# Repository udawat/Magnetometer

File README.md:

Magnetometer
============

Honeywell’s HMC5883L 3-Axis Magnetometer can measure both the direction and the magnitude of Earth’s magnetic fields. Think of it as a Digital Compass.

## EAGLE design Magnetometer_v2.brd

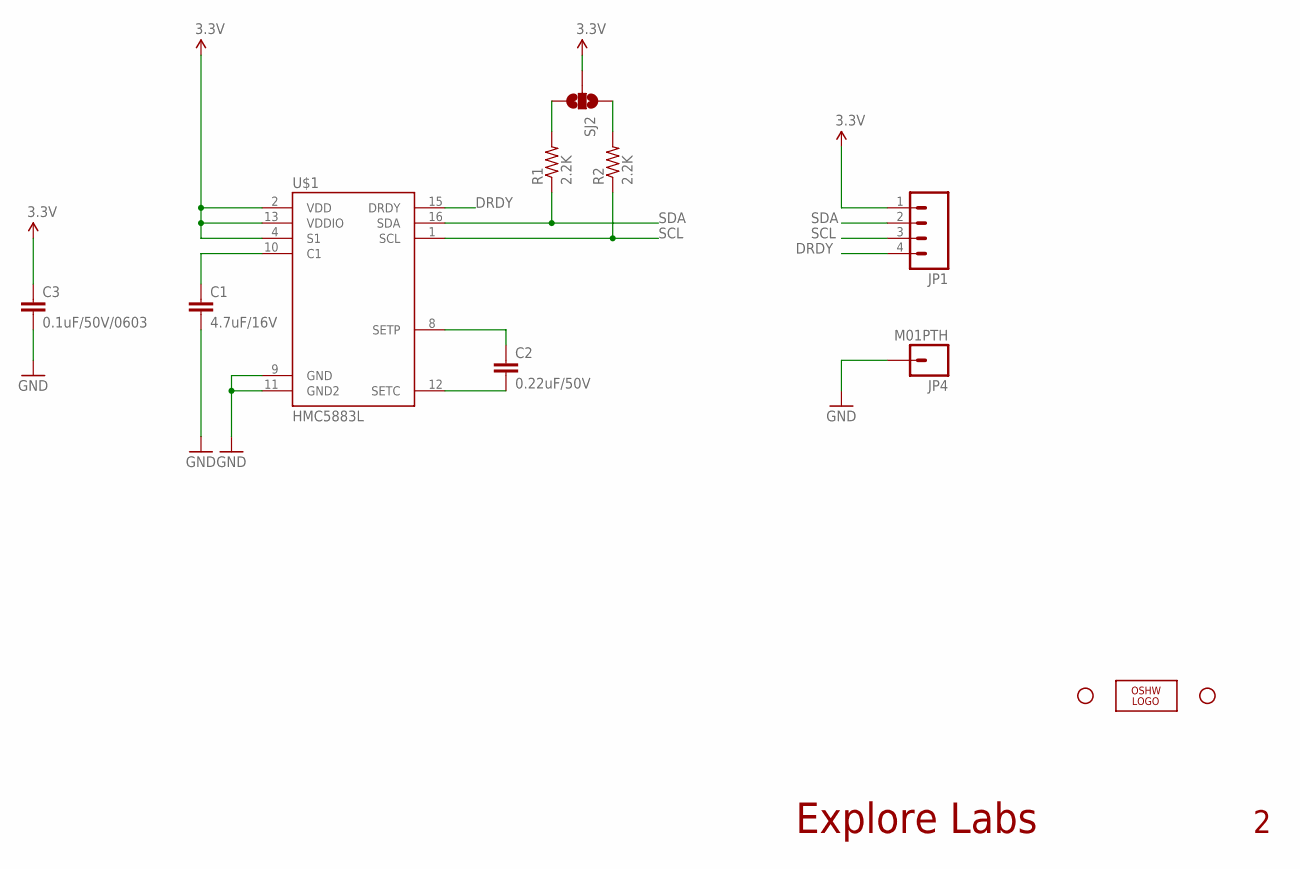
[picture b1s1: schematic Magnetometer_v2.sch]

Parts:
C1: 4.7uF/16V; 1206
C2: 0.22uF/50V; 1206
C3: 0.1uF/50V/0603; 0603-CAP
JP1: M04PTH; 1X04
JP2, JP3: STAND-OFFTIGHT; STAND-OFF-TIGHT
JP4: M01PTH; 1X01
LOGO1: OSHW_LOGO_FILLX0150-NT; OSHW_FILLX150_NOTEXT
R1, R2: 2.2K; 0603-RES
SJ2: SOLDERJUMPER_2WAYS; SJ_3
U$1: HMC5883L; LPCC16

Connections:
3.3V: C3.1, JP1.1, SJ2.2, U$1.2 (VDD), U$1.4 (S1), U$1.13 (VDDIO)
DRDY: JP1.4, U$1.15 (DRDY)
GND: C1.2, C3.2, JP4.1, U$1.9 (GND), U$1.11 (GND2)
unnamed: C2.1, U$1.8 (SETP)
unnamed: C1.1, U$1.10 (C1)
unnamed: R1.2, SJ2.3
unnamed: R2.2, SJ2.1
unnamed: C2.2, U$1.12 (SETC)
SCL: JP1.3, R2.1, U$1.1 (SCL)
SDA: JP1.2, R1.1, U$1.16 (SDA)

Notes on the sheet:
Explore Labs

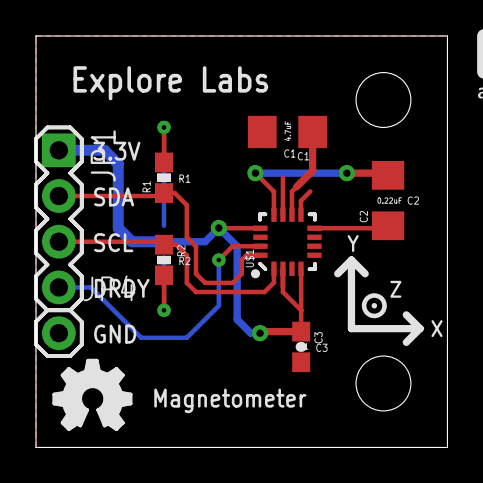
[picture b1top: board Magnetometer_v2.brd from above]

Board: 2 copper layers, 22.9 x 22.9 mm, 13 parts (1 on the bottom side), 10 nets.

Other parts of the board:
U$2: EXLABS_LOGO_0.25

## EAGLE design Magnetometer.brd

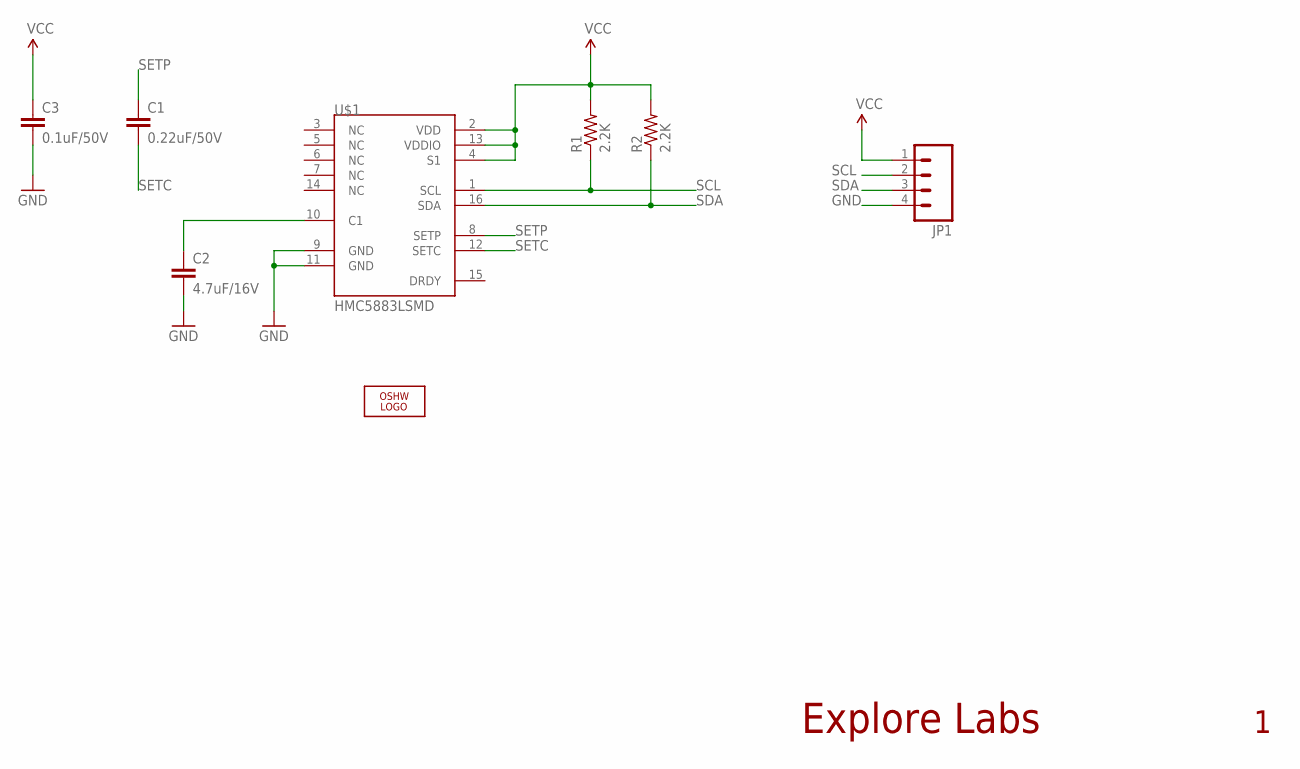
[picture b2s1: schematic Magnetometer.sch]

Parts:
C1: 0.22uF/50V; 1206
C2: 4.7uF/16V; 1206
C3: 0.1uF/50V; 0805
JP1: M04PTH; 1X04
LOGO1: OSHW_LOGO_FILLX0100-NT; OSHW_FILLX100_NOTEXT
R1, R2: 2.2K; 0603-RES
U$1: HMC5883LSMD; 16LPCC

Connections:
GND: C2.2, C3.2, JP1.4, U$1.9 (GND), U$1.11 (GND)
unnamed: C2.1, U$1.10 (C1)
SCL: JP1.2, R1.1, U$1.1 (SCL)
SDA: JP1.3, R2.1, U$1.16 (SDA)
SETC: C1.2, U$1.12 (SETC)
SETP: C1.1, U$1.8 (SETP)
VCC: C3.1, JP1.1, R1.2, R2.2, U$1.2 (VDD), U$1.4 (S1), U$1.13 (VDDIO)

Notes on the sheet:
Explore Labs

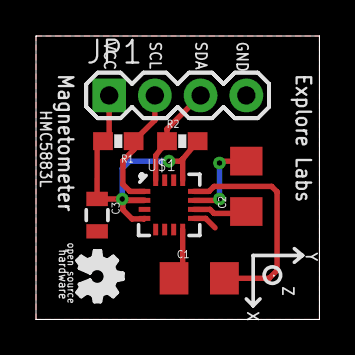
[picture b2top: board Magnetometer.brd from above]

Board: 2 copper layers, 15.7 x 15.7 mm, 8 parts (0 on the bottom side), 7 nets.

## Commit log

2012-11-23 initial commit
    CAD files for Magnetometer including the final Gerber data
2013-01-21 Updated to Magnetometer version 2
    New Gerber Data for v2
2013-01-31 added schematic in pdf format

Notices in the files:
parts and their libraries:
SparkFun-Sensors: Licensing: CC v3.0 Share-Alike You are welcome to use this library for commercial purposes.
SparkFun-Aesthetics: Released under the Creative Commons
SparkFun-Aesthetics: http://creativecommons.org/licenses/by-sa/3.0
